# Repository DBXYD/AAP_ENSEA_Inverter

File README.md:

# ENSEA - Projet Onduleur Triphasé didactique, 60V, 10A
- Rédaction : Nicolas Papazoglou, Alexis Martin,
- Desgin et Réalisation : Nicolas Papazoglou, Alexis Martin, Patricia Kittel,
- Conseils : Pierre Toussaint.

# Présentation du projet

## Motivations
Dans le cadre de la formation des étudiants de l'ENSEA, les professeurs ont ressenti le besoin de créer une maquette pédagogique pour plusieurs raisons : 
* De nombreuses pannes récurentes sur les maquettes existantes,
* Réparations chronophages voir impossibles,
* L'ensemble du matériel est caché des étudiants, ils ne peuvent pas voir l'intérieur, le routage de la carte et les composants,
* Le coût de l'ensemble du matériel acheté est important.

## Objectifs
* Réalisation d'une maquette fiable pour les TPs d’électrotechnique et automatique : Gain en temps et en autonomie pour les étudiants,
* Feedback automatique en fonction des erreurs détectées : Gain en autonomie pour les étudiants, possibilité de travail hors séance sans
supervision d’un professeur,
* Projet open-source (disponible sur github),
* Compréhension globale possible par les étudiants, application de l’ensemble de leurs cours dans une maquette,
* Création modulaire, réutilisable dans d’autres cours/projets,
* Evolution possible à d’autres enseignements (buck/boost, 4Q, brushless, moteurs synchrones, asservissement, etc...),
* Maintenance facile et rapide

## Cahier des charges
* Onduleur triphasé 60V / 15A,
* Protections surtensions et surintensités,
* Commande de mise sous tension,
* Pilotage par liaison UART over USB,
* Utilisable en commande “brushless” : entrées position “hall” ,
* Utilisable en commande vectorielle ou MCC : entrée position “encoder”,
* Protection alimentation non réversible : module “freinage”,
* Vérification automatique des temps morts,
* Mesure de courants (hall) dans les 3 phases + entrée,
* Mesure de tension dans les 3 phases + entrée,
* Alimentation externe secteur,
* Affichage erreurs, intensité PWM (affiche externe),
* Sorties mesures de courants et PWMs,
* Boitier,
* Tenue thermique,
* Isolation galvanique.

# Guide d'utilisation

# Guide du développeur
La majorité des signaux sont disponibles sur les connecteurs morpho au format des cartes Nucleo-64.
Sur la base des cartes Nucleo, les connecteurs répérés CN7 et CN10 sont disponibles pour intégrer une carte custom.

## Connecteurs
### Connecteur CN7
| Type           | Label         | Pin number | Pin number | Label         | Type           |
|----------------|---------------|------------|------------|---------------|----------------|
| Digital Output | UART_TX_STM32 | 1          | 2          | UART_RX_STM32 | Digital Input  |
|                | N.C.          | 3          | 4          | NRST_STM32    | Digital Output |
|                | N.C.          | 5          | 6          | 5V            | Power Input    |
|                | N.C.          | 7          | 8          | GND           | Power Input    |
|                | N.C.          | 9          | 10         | N.C           |                |
|                | N.C.          | 11         | 12         | N.C           |                |
|                | N.C.          | 13         | 14         | N.C.          |                |
|                | N.C.          | 15         | 16         | N.C.          |                |
|                | N.C.          | 17         | 18         | N.C.          |                |
| Power Input    | GND           | 19         | 20         | GND           | Power Input    |
|                | N.C.          | 21         | 22         | GND           | Power Input    |
|                | N.C.          | 23         | 24         | N.C.          |                |
|                | N.C.          | 25         | 26         | N.C.          |                |
|                | N.C.          | 27         | 28         | Bus_V         | Analog Input   |
|                | N.C.          | 29         | 30         | U_Imes        | Analog Input   |
|                | N.C.          | 31         | 32         | Enc_B         | Digital Input  |
|                | N.C.          | 33         | 34         | W_Imes        | Analog Input   |
| Analog Input   | Bus_Imes      | 35         | 36         | W_Vph         | Analog Input   |
| Analog Input   | V_Vph         | 37         | 38         | U_Vph         | Analog Input   |

### Connecteur CN10
| Type           | Label         | Pin number |            | Label         | Type           |
|----------------|---------------|------------|------------|---------------|----------------|
|                | N.C.          | 1          | 2          | Enc_Z         | Digital Input  |
|                | N.C.          | 3          | 4          | N.C.          |                |
|                | N.C.          | 5          | 6          | N.C.          |                |
|                | N.C.          | 7          | 8          | N.C.          |                |
| Power Input    | GND           | 9          | 10         | N.C.          |                |
|                | N.C.          | 11         | 12         | N.C.          |                |
| Digital Input  | Enc_A         | 13         | 14         | N.C.          |                |
|                | N.C.          | 15         | 16         | N.C.          |                |
|                | N.C.          | 17         | 18         | N.C.          |                |
|                | N.C.          | 19         | 20         | GND           | Power Input    |
| Output         | V_PWM_H       | 21         | 22         | N.C.          |                |
| Output         | U_PWM_H       | 23         | 24         | V_Imes        | Analog Input   |
|                | N.C.          | 25         | 26         | W_PWM_L       | Output         |
|                | N.C.          | 27         | 28         | V_PWM_L       | Output         |
|                | N.C.          | 29         | 30         | U_PWM_L       | Output         |
|                | N.C.          | 31         | 32         | GND           | Power Input    |
| Output         | W_PWM_H       | 33         | 34         | N.C.          |                |
|                | N.C.          | 35         | 36         | N.C.          |                |
|                | N.C.          | 37         | 38         | N.C.          |                |

## Input / Output labels

### Communication avec le micro-controleur présent sur la carte-mère
* UART_TX_STM32 : UART vers le micro-controleur
* UART_RX_STM32 : UART depuis le micro-controleur
* NRST_STM32 : signal pour faire un reset du micro-controleur de la carte

### Communication avec le module encodeur
* Enc_A : entrée du signal A de l'encodeur
* Enc_B : entrée du signal B de l'encodeur
* Enc_Z : entrée du signal Z de l'encodeur

### Mesure de tension
* Bus_V : mesure de la tension du bus d'alimentation
* U_Vph : mesure de la tension de la sortie U (entre les 2 transistors)
* V_Vph : mesure de la tension de la sortie V (entre les 2 transistors)
* W_Vph : mesure de la tension de la sortie W (entre les 2 transistors)

### Mesure de courant
* Bus_Imes : mesure de courant du bus d'alimentation
* U_Imes
* V_Imes
* W_Imes

### Génération de PWM
* U_PWM_H
* U_PWM_L
* V_PWM_H
* V_PWM_L
* W_PWM_H
* W_PWM_L

# FAQ

# Pannes courantes 
## Dysfonctionnement des Mosfet
Plusieurs causes peuvent causer la destruction des transistors : 
* Non respect des temps mort,
* Commande provocant une freinage trop important : retour du courant chargeant les condensateurs sur le bus d'alimentation. Ceci provoque la montée en tension du bus au-delà des spécifications des transistor de puissance

Détection de la panne : 
* Débrancher l'ensemble des câbles de la maquette, et le cas échéant, attendre que les condensateurs du bus d'alimentation soient totalement vides.
* A l'aide d'un multimètre, en mode diode, tester la continuité entre :
  - Entre la sortie U et le bus d'alimentation (Q202)
  - Entre la sortie U et la masse (Q203)
  - Entre la sortie V et le bus d'alimentation (Q302)
  - Entre la sortie V et la masse (Q303)
  - Entre la sortie W et le bus d'alimentation (Q402)
  - Entre la sortie W et la masse (Q403)
* Le fonctionnement normal est l'absence de continuité électrique. Dans le cas d'une continuité, le transistor en question est HS, il doit donc être changé.

# Composants
* Drivers de Mosfet/optocoupleur : HCPL-315J, Optocoupleurs sortie logique 0.5A IGBT Gate Drive [link](https://www.mouser.fr/ProductDetail/Broadcom-Avago/HCPL-315J?qs=s%252BgfxR24RQ4lntGToXJAvA%3D%3D)
* Transistor MOSFET : IRF540NPBF, MOSFET de puissance, Canal N, 100 V, 33 A, 0.044 ohm, TO-220AB, Traversant [Link](https://fr.farnell.com/infineon/irf540npbf/transistor-mosfet-canal-n-to220/dp/8648298?st=irf540n)
* Capteur de Courant : GO 10-SME/SP3, Capteur de courant, 300 kHz, SOIC, 8 Broche(s), 3.135 V, 3.465 V [Link](https://fr.farnell.com/lem/go-10-sme-sp3/capteur-courant-300khz-soic-8/dp/3796461?st=GO%2010-SME/SP3)
* Power supply : MP-LD30-23B15R2 - Alimentation montage PCB AC/DC (PSU), ITE, Équipements Ménagers et Transformateurs, 1 sortie [link](https://fr.farnell.com/multicomp-pro/mp-ld30-23b15r2/power-supply-ac-dc-15v-2a/dp/3780527)
* Power regulator : Input : 5V DC, Output : 3.3V DC, AZ1117CH-3.3TRG1 - LDO, FIXE, 3,3V, 0.8A, -20 A 125°C [link](https://fr.farnell.com/diodes-inc/az1117ch-3-3trg1/ldo-fixe-3-3v-0-8a-20-a-125-c/dp/3483073RL)
* Alimentation 15V/400mA isolé : MPRB2415S-6W - Conv. DC/DC, montage traversant isolé, ITE, 4:1, 6 W, 1 sortie, 15 V, 400 mA [link](https://fr.farnell.com/multicomp-pro/mprb2415s-6w/convertisseur-dc-dc-15v-0-4a/dp/3652723)
* Alimentation 5V/200mA isolé : 17791063215 - MagI³C-VISM Variable Isolated SIP Module, [Link](https://www.we-online.com/components/products/datasheet/17791063215.pdf)
* Connector : PX0580/PC Connecteur de puissance IEC, Entrée IEC C14, 10 A, 250 VAC, Traversant [link](https://fr.farnell.com/bulgin/px0580-pc/embase-iec-c14-carte-proto-10a/dp/313853)
* Screen : MDOB128064XV-YI - OLED graphique, 128 x 64 pixels, Jaune sur noir, 3.3V, I2C, 35.5mm x 32mm, -40 °C [Link](https://fr.farnell.com/midas/mdob128064xv-yi/afficheur-oled-cob-128-x-64-pix/dp/3407293)
* Break resistor : 162-3488 - Résistance à montage sur châssis Aluminium, 5Ω 100W ±1% [Link](https://fr.rs-online.com/web/p/resistances-a-montage-sur-chassis/1623488)
* Break schottky : VS-15TQ060S-M3 - Redresseur Schottky, 60 V, 15 A, Une, TO-263AB, 3 Broche(s), 620 mV [Link](https://fr.farnell.com/vishay/vs-15tq060s-m3/diode-schottky-simple-60v-to263ab/dp/2909608?ost=2909608)

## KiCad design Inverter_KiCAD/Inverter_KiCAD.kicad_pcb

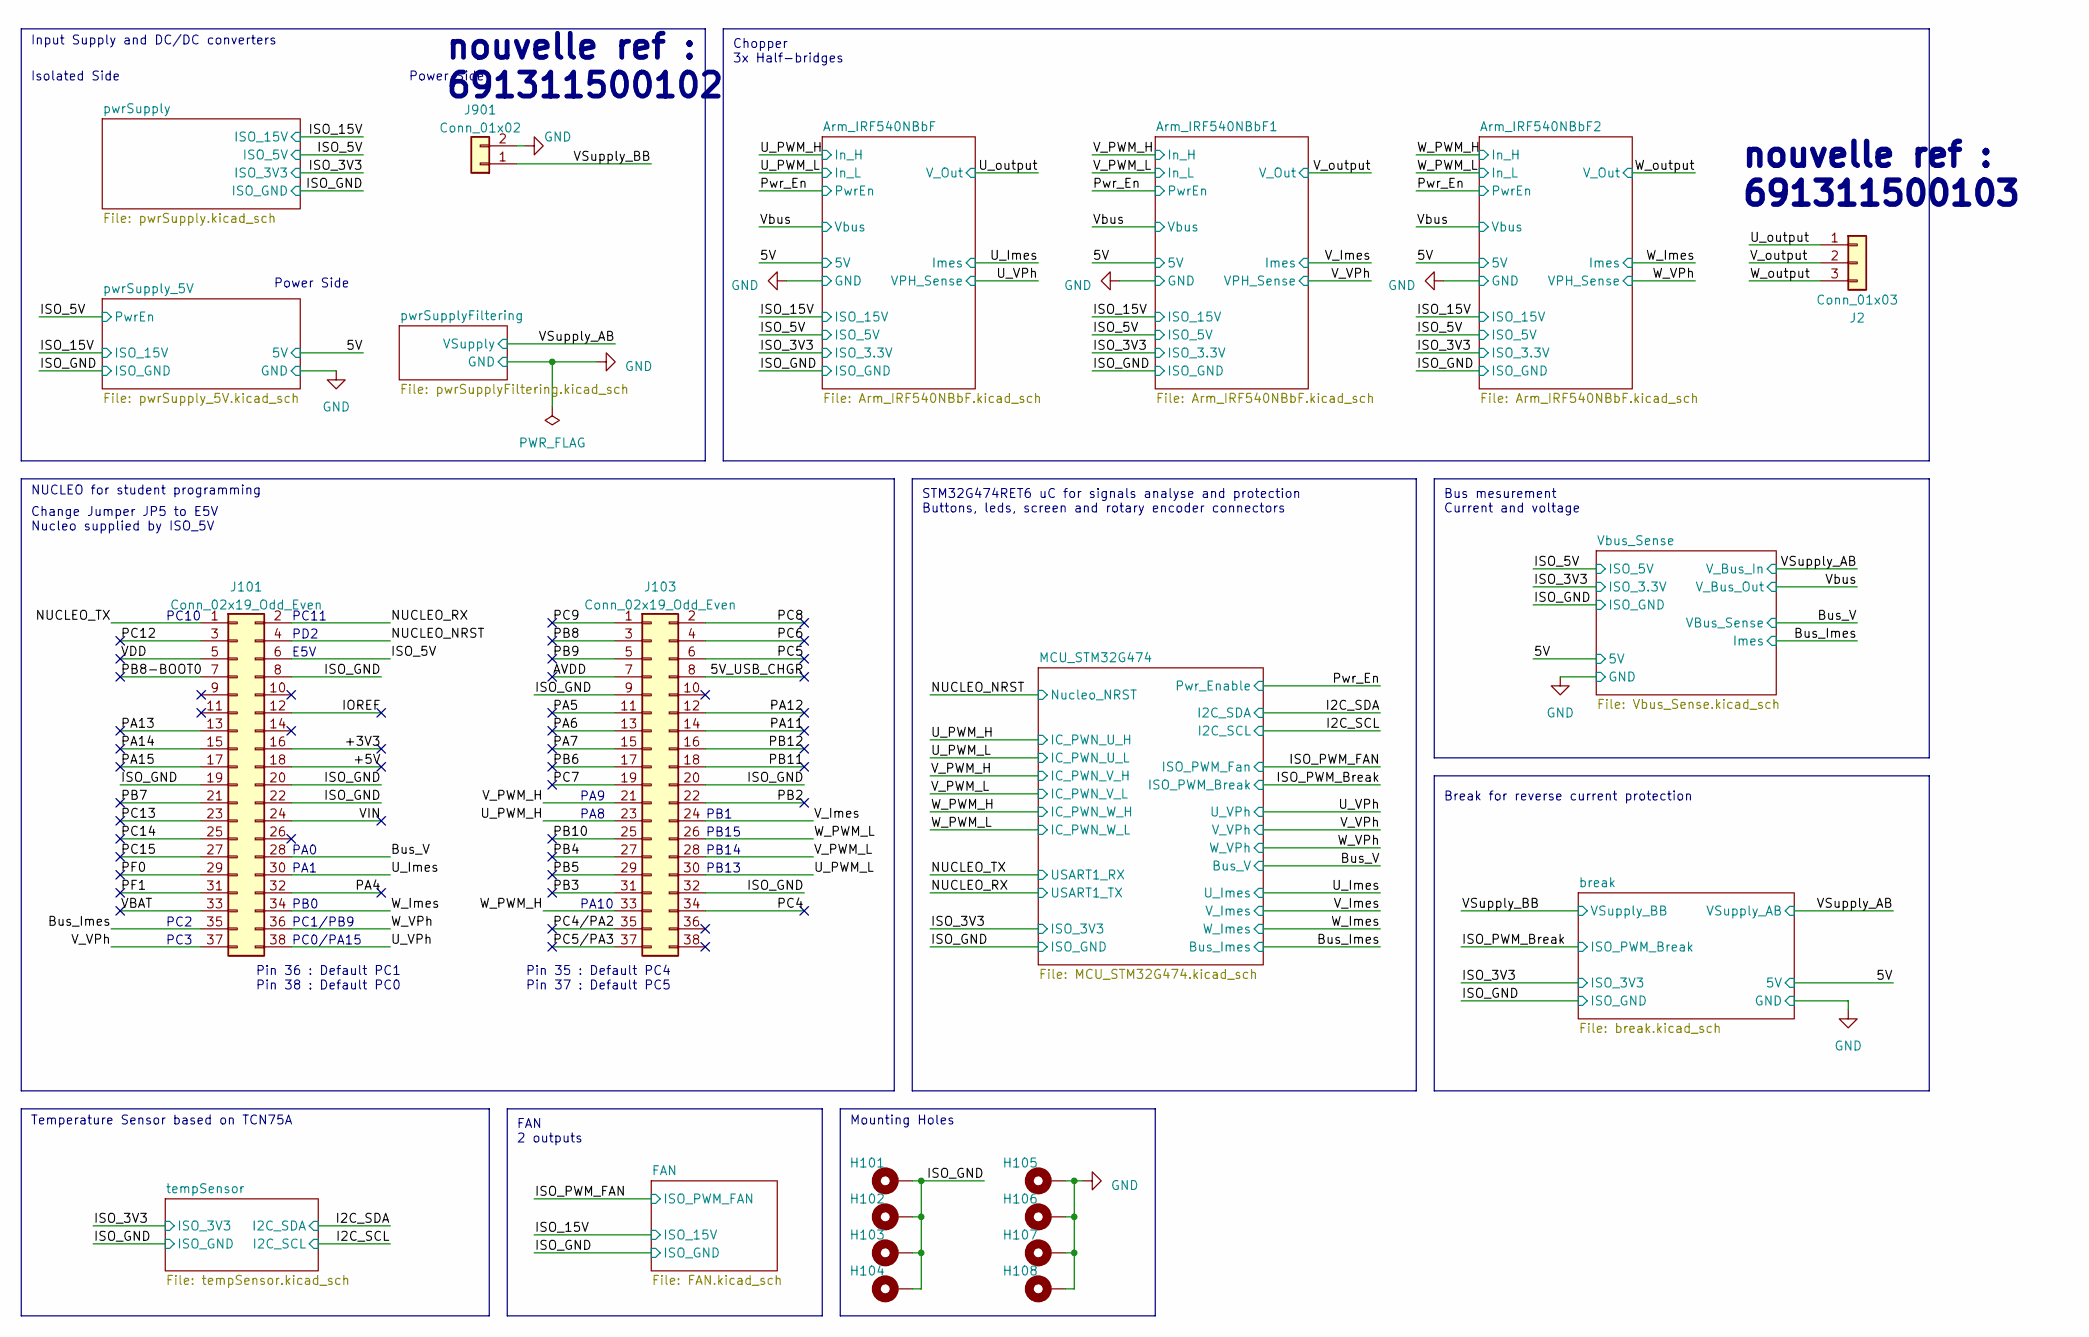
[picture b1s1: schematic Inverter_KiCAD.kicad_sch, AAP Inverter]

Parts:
H101, H102, H103, H104, H105, H106, H107, H108: MountingHole_Pad; MountingHole_3.2mm_M3_Pad_Via
J2: Conn_01x03; 691311700003
J101, J103: Conn_02x19_Odd_Even; PinHeader_2x19_P2.54mm_Vertical
J901: Conn_01x02; 691311700002

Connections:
/5V_USB_CHGR: J103.8
/+3V3: J101.16
/+5V: J101.18
/AVDD: J103.7
/Bus_Imes: J101.35; also elsewhere on the board
/Bus_V: J101.28; also elsewhere on the board
/IOREF: J101.12
/ISO_5V: J101.6; also elsewhere on the board
/ISO_GND: H101.1, H102.1, H103.1, H104.1, J101.8, J101.19, J101.20, J101.22, J103.9, J103.20, J103.32; also elsewhere on the board
/NUCLEO_NRST: J101.4; also elsewhere on the board
/NUCLEO_RX: J101.2; also elsewhere on the board
/NUCLEO_TX: J101.1; also elsewhere on the board
/PA4: J101.32
/PA5: J103.11
/PA6: J103.13
/PA7: J103.15
/PA11: J103.14
/PA12: J103.12
/PA13: J101.13
/PA14: J101.15
/PA15: J101.17
/PB2: J103.22
/PB3: J103.31
/PB4: J103.27
/PB5: J103.29
/PB6: J103.17
/PB7: J101.21
/PB8: J103.3
/PB8-BOOT0: J101.7
/PB9: J103.5
/PB10: J103.25
/PB11: J103.18
/PB12: J103.16
/PC4: J103.34
/PC4/PA2: J103.35
/PC5: J103.6
/PC5/PA3: J103.37
/PC6: J103.4
/PC7: J103.19
/PC8: J103.2
/PC9: J103.1
/PC12: J101.3
/PC13: J101.23
/PC14: J101.25
/PC15: J101.27
/PF0: J101.29
/PF1: J101.31
/U_Imes: J101.30; also elsewhere on the board
/U_PWM_H: J103.23; also elsewhere on the board
/U_PWM_L: J103.30; also elsewhere on the board
/U_VPh: J101.38; also elsewhere on the board
/U_output: J2.1; also elsewhere on the board
/VBAT: J101.33
/VDD: J101.5
/VIN: J101.24
/V_Imes: J103.24; also elsewhere on the board
/V_PWM_H: J103.21; also elsewhere on the board
/V_PWM_L: J103.28; also elsewhere on the board
/V_VPh: J101.37; also elsewhere on the board
/V_output: J2.2; also elsewhere on the board
/W_Imes: J101.34; also elsewhere on the board
/W_PWM_H: J103.33; also elsewhere on the board
/W_PWM_L: J103.26; also elsewhere on the board
/W_VPh: J101.36; also elsewhere on the board
/W_output: J2.3; also elsewhere on the board
/break/Break_Drain_Mosfet: J901.1; also elsewhere on the board

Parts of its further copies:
J1: Conn_01x02; 691311700002

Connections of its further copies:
/VSupply_BB: J1.1; also elsewhere on the board

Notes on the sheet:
PB14
PC10
Input Supply and DC/DC converters
Temperature Sensor based on TCN75A
PC3
nouvelle ref : 691311500103
PA8
Mounting Holes
NUCLEO for student programming
Pin 35 : Default PC4 Pin 37 : Default PC5
PA10
STM32G474RET6 uC for signals analyse and protection Buttons, leds, screen and rotary encoder connectors
Break for reverse current protection
PB13
Chopper 3x Half-bridges
PA0
PC0/PA15
PD2
nouvelle ref : 691311500102
E5V
PB0
PA9
Power Side
Isolated Side
PC11
FAN 2 outputs
PA1
Pin 36 : Default PC1 Pin 38 : Default PC0
PC1/PB9
PB1
PC2
Bus mesurement Current and voltage
PB15
Change Jumper JP5 to E5V Nucleo supplied by ISO_5V

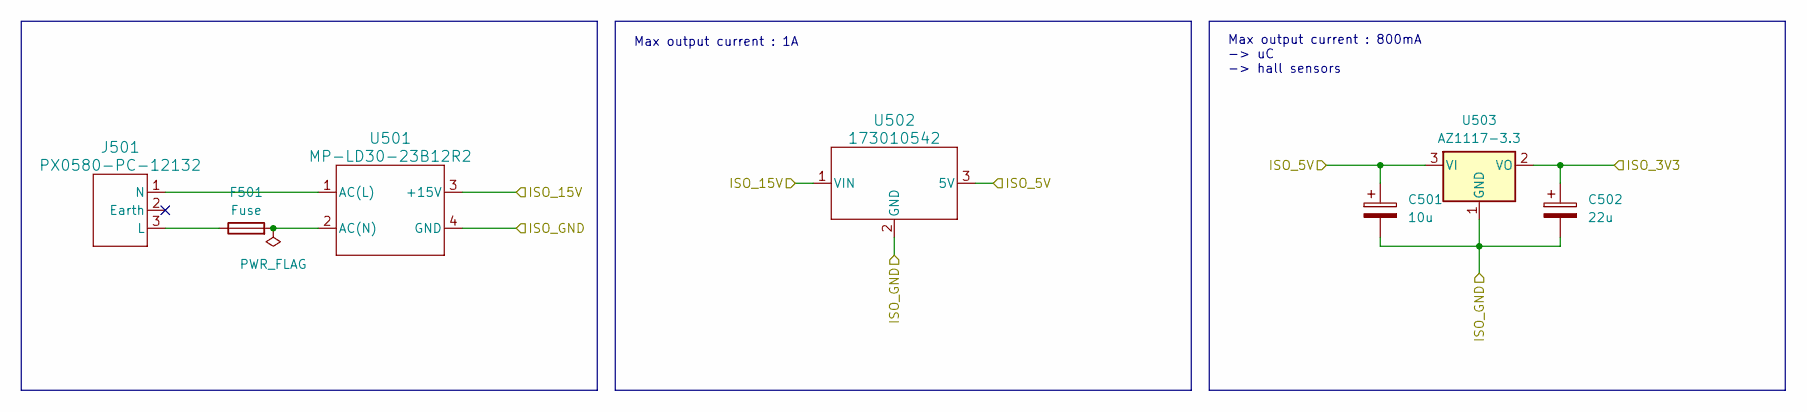
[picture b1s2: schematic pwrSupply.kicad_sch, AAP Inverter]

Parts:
C501: 10u; CP_Elec_4x5.4
C502: 22u; CP_Elec_5x5.4
F501: Fuse; 0031.8201
J501: PX0580-PC-12132
U501: MP-LD30-23B12R2; MP-LD30-23B15R2
U502: 173010542; 173010578
U503: AZ1117-3.3; SOT-223-3_TabPin2

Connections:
/ISO_3V3: C502.1, U503.2 (VO); also elsewhere on the board
/ISO_5V: C501.1, U502.3 (5V), U503.3 (VI); also elsewhere on the board
/ISO_15V: U501.3 (+15V), U502.1 (VIN); also elsewhere on the board
/ISO_GND: C501.2, C502.2, U501.4 (GND), U502.2 (GND), U503.1 (GND); also elsewhere on the board
unnamed: F501.1, J501.3 (L)
unnamed: J501.1 (N), U501.1 (AC(L))
unnamed: F501.2, U501.2 (AC(N))

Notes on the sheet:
Max output current : 800mA -> uC -> hall sensors
Max output current : 1A

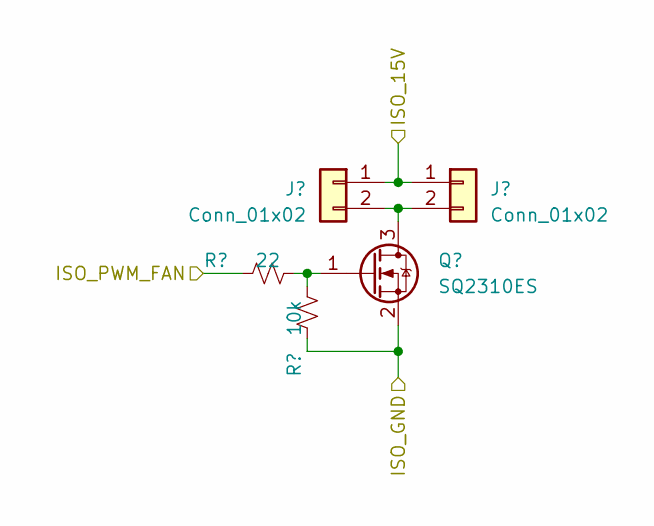
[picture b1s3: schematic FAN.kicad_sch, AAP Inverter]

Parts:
J1101, J1102: Conn_01x02; JST_XH_B2B-XH-A_1x02_P2.50mm_Vertical
Q1101: SQ2310ES; SOT-23
R1101: 22; R_0402_1005Metric_Pad0.72x0.64mm_HandSolder
R1102: 10k; R_0402_1005Metric_Pad0.72x0.64mm_HandSolder

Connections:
/ISO_15V: J1101.1, J1102.1; also elsewhere on the board
/ISO_GND: Q1101.2 (S), R1102.2; also elsewhere on the board
/ISO_PWM_FAN: R1101.2; also elsewhere on the board
unnamed: J1101.2, J1102.2, Q1101.3 (D)
unnamed: Q1101.1 (G), R1101.1, R1102.1

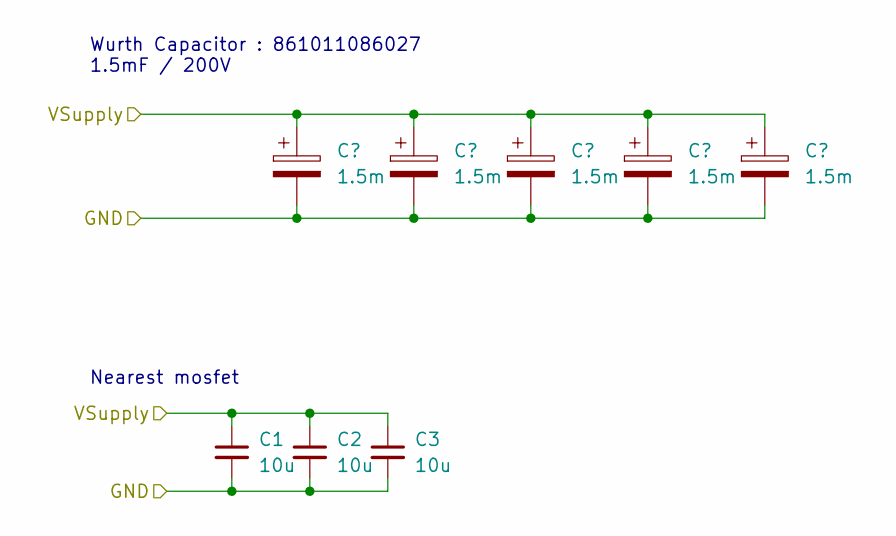
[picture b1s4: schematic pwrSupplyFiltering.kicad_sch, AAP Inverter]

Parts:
C1, C2, C3: 10u; C_0805_2012Metric
C1005, C1006, C1007, C1008, C1009: 1.5m; CP_Radial_D35.0mm_P10.00mm_SnapIn

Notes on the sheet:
Wurth Capacitor : 861011086027 1.5mF / 200V
Nearest mosfet

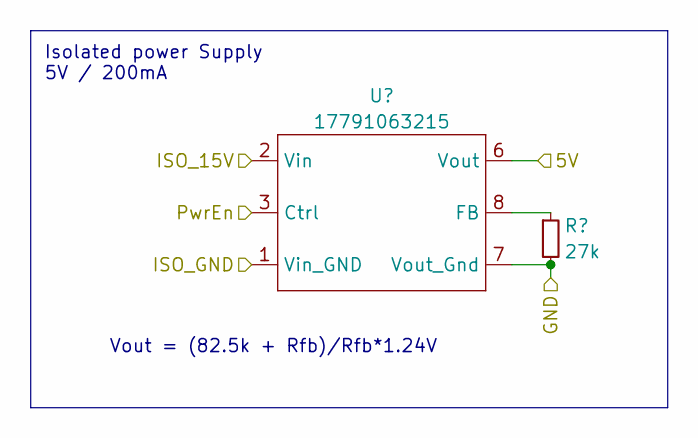
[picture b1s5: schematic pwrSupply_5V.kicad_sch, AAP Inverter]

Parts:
R701: 27k; R_0402_1005Metric_Pad0.72x0.64mm_HandSolder
U701: 17791063215

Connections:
/5V: U701.6 (Vout); also elsewhere on the board
/ISO_5V: U701.3 (Ctrl); also elsewhere on the board
/ISO_15V: U701.2 (Vin); also elsewhere on the board
/ISO_GND: U701.1 (Vin_GND); also elsewhere on the board
unnamed: R701.1, U701.8 (FB)

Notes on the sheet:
Vout = (82.5k + Rfb)/Rfb*1.24V
Isolated power Supply 5V / 200mA

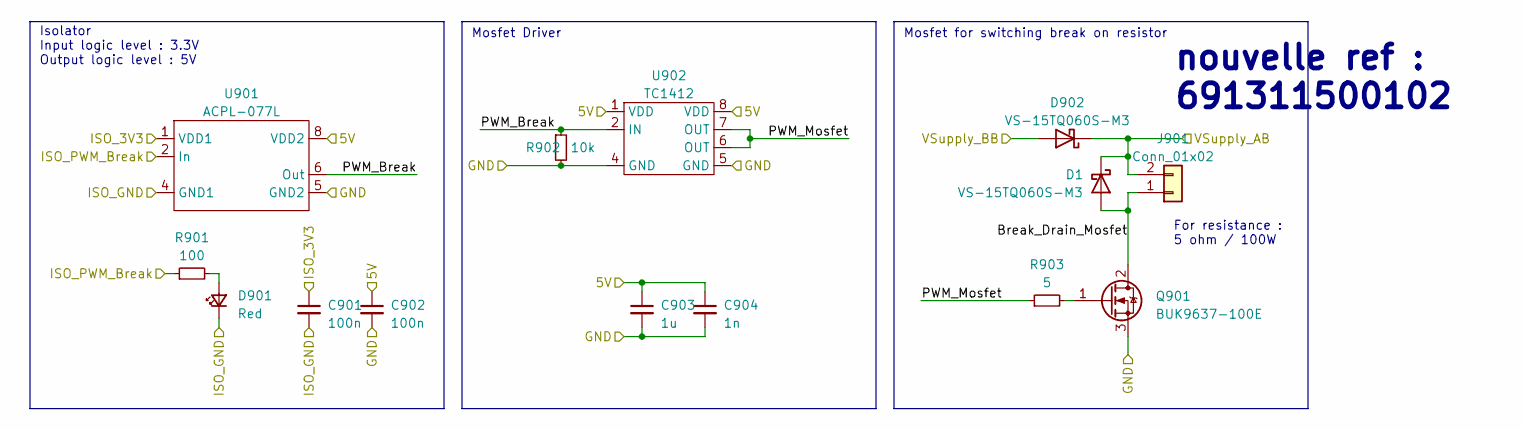
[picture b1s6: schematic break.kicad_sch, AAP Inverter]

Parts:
C901, C902: 100n; C_0402_1005Metric_Pad0.74x0.62mm_HandSolder
C903: 1u; C_0402_1005Metric_Pad0.74x0.62mm_HandSolder
C904: 1n; C_0402_1005Metric_Pad0.74x0.62mm_HandSolder
D1, D902: VS-15TQ060S-M3; TO-263-2
D901: Red; LED_0603_1608Metric_Pad1.05x0.95mm_HandSolder
J901: Conn_01x02; 691311700002
Q901: BUK9637-100E; TO-263-2
R901: 100; R_0402_1005Metric_Pad0.72x0.64mm_HandSolder
R902: 10k; R_0402_1005Metric_Pad0.72x0.64mm_HandSolder
R903: 5; R_1206_3216Metric_Pad1.30x1.75mm_HandSolder
U901: ACPL-077L; SO-8_3.9x4.9mm_P1.27mm
U902: TC1412; SOIC-8_3.9x4.9mm_P1.27mm

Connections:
/5V: C902.1, C903.1, C904.1, U901.8 (VDD2), U902.1 (VDD), U902.8 (VDD); also elsewhere on the board
/ISO_3V3: C901.1, U901.1 (VDD1); also elsewhere on the board
/ISO_GND: C901.2, D901.1 (K), U901.4 (GND1); also elsewhere on the board
/ISO_PWM_Break: R901.1, U901.2 (In); also elsewhere on the board
/VSupply_BB: D902.3 (A); also elsewhere on the board
/break/Break_Drain_Mosfet: D1.3 (A), J901.1, Q901.2 (D)
/break/PWM_Break: R902.1, U901.6 (Out), U902.2 (IN)
/break/PWM_Mosfet: R903.1, U902.6 (OUT), U902.7 (OUT)
unnamed: D901.2 (A), R901.2
unnamed: Q901.1 (G), R903.2

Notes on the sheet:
Isolator Input logic level : 3.3V Output logic level : 5V
nouvelle ref : 691311500102
For resistance : 5 ohm / 100W
Mosfet for switching break on resistor
Mosfet Driver

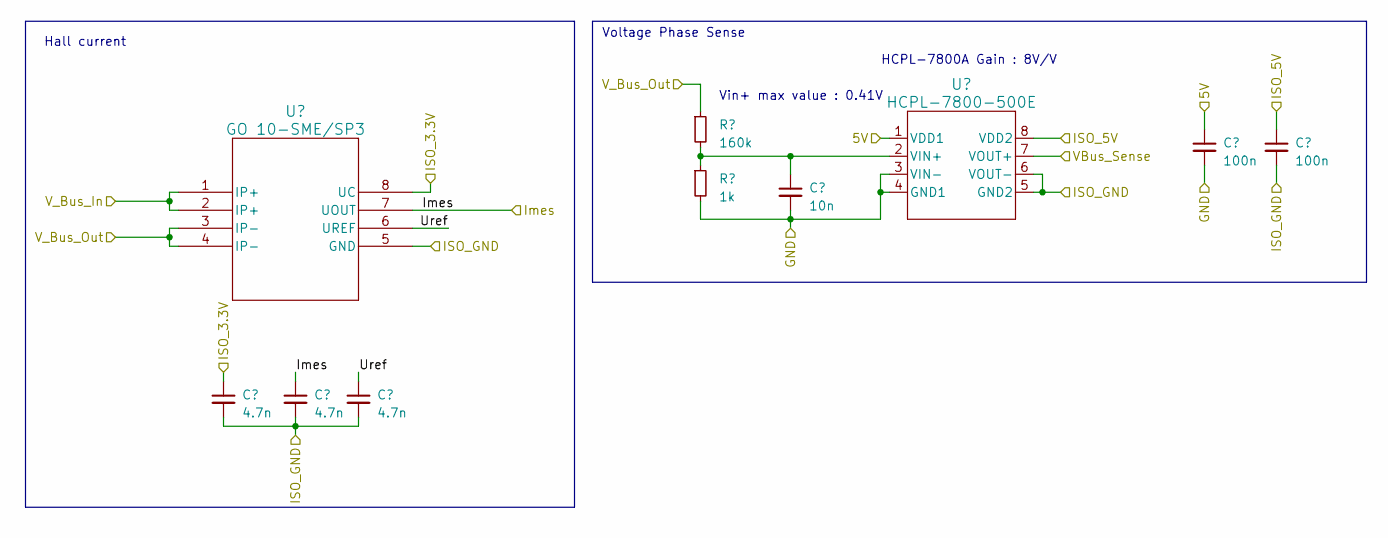
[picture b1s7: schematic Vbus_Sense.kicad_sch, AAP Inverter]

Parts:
C601, C602, C603: 4.7n; C_0402_1005Metric_Pad0.74x0.62mm_HandSolder
C604: 10n; C_0402_1005Metric_Pad0.74x0.62mm_HandSolder
C605, C606: 100n; C_0402_1005Metric_Pad0.74x0.62mm_HandSolder
R601: 160k; R_0402_1005Metric_Pad0.72x0.64mm_HandSolder
R602: 1k; R_0402_1005Metric_Pad0.72x0.64mm_HandSolder
U601: GO 10-SME/SP3; SOIC8-GO-SME&slash_SP3_LEM
U602: HCPL-7800-500E; DIP-8 Gull Wing

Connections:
/5V: C605.1, U602.1 (VDD1); also elsewhere on the board
/Bus_Imes: C602.1, U601.7 (UOUT); also elsewhere on the board
/Bus_V: U602.7 (VOUT+); also elsewhere on the board
/ISO_3V3: C601.1, U601.8 (UC); also elsewhere on the board
/ISO_5V: C606.1, U602.8 (VDD2); also elsewhere on the board
/ISO_GND: C601.2, C602.2, C603.2, C606.2, U601.5 (GND), U602.5 (GND2), U602.6 (VOUT-); also elsewhere on the board
/Vbus: R601.1, U601.3 (IP-), U601.4 (IP-); also elsewhere on the board
/Vbus_Sense/Uref: C603.1, U601.6 (UREF)
unnamed: C604.1, R601.2, R602.1, U602.2 (VIN+)

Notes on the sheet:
Hall current
Vin+ max value : 0.41V
HCPL-7800A Gain : 8V/V
Voltage Phase Sense

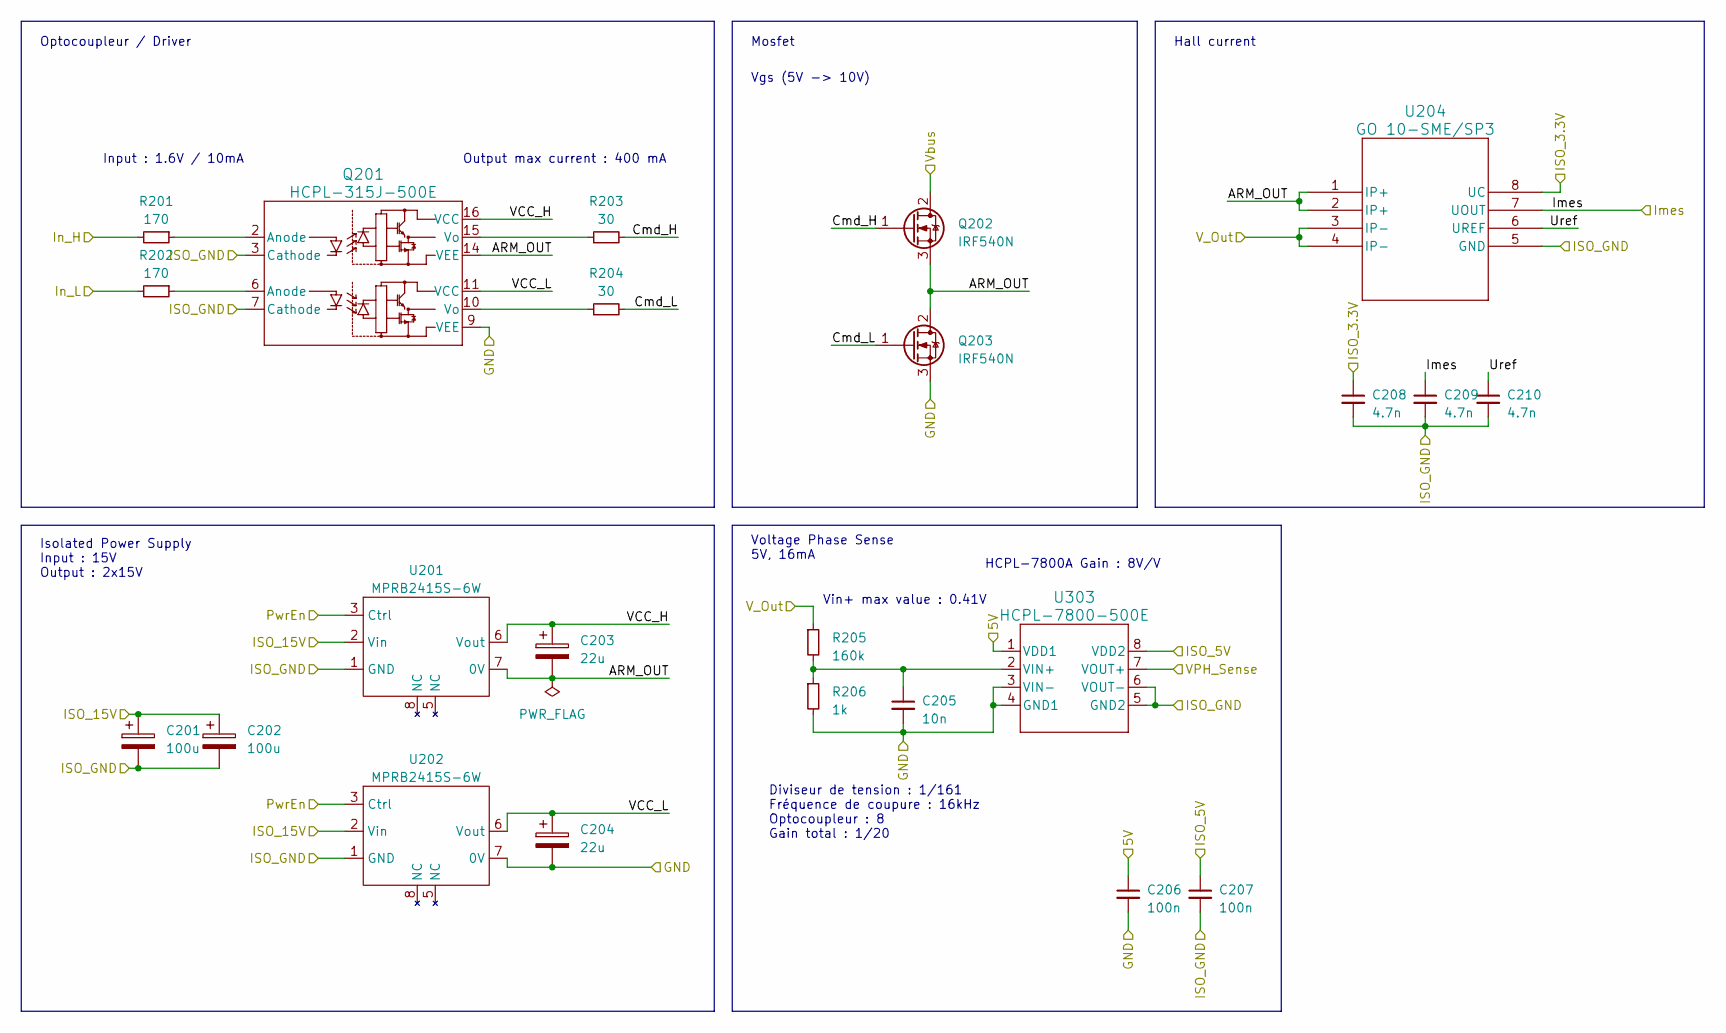
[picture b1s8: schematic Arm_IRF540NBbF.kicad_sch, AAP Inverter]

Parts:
C201, C202: 100u; CP_Elec_6.3x7.7
C203, C204: 22u; CP_Elec_5x5.4
C205: 10n; C_0402_1005Metric_Pad0.74x0.62mm_HandSolder
C206, C207: 100n; C_0402_1005Metric_Pad0.74x0.62mm_HandSolder
C208, C209, C210: 4.7n; C_0402_1005Metric_Pad0.74x0.62mm_HandSolder
Q201: HCPL-315J-500E; SO-16_HCPL-315J_BRA
Q202, Q203: IRF540N; TO-220-3_Vertical
R201, R202: 170; R_0402_1005Metric_Pad0.72x0.64mm_HandSolder
R203, R204: 30; R_1206_3216Metric_Pad1.30x1.75mm_HandSolder
R205: 160k; R_0402_1005Metric_Pad0.72x0.64mm_HandSolder
R206: 1k; R_0402_1005Metric_Pad0.72x0.64mm_HandSolder
U201, U202: MPRB2415S-6W; MPRB2415S
U204: GO 10-SME/SP3; SOIC8-GO-SME&slash_SP3_LEM
U303: HCPL-7800-500E; DIP-8 Gull Wing

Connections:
/5V: C206.1, U303.1 (VDD1); also elsewhere on the board
/Arm_IRF540NBbF/ARM_OUT: C203.2, Q201.14 (VEE), Q202.3 (S), Q203.2 (D), U201.7 (0V), U204.1 (IP+), U204.2 (IP+)
/Arm_IRF540NBbF/Cmd_H: Q202.1 (G), R203.2
/Arm_IRF540NBbF/Cmd_L: Q203.1 (G), R204.2
/Arm_IRF540NBbF/Uref: C210.1, U204.6 (UREF)
/Arm_IRF540NBbF/VCC_H: C203.1, Q201.16 (VCC), U201.6 (Vout)
/Arm_IRF540NBbF/VCC_L: C204.1, Q201.11 (VCC), U202.6 (Vout)
/ISO_3V3: C208.1, U204.8 (UC); also elsewhere on the board
/ISO_5V: C207.1, U303.8 (VDD2); also elsewhere on the board
/ISO_15V: C201.1, C202.1, U201.2 (Vin), U202.2 (Vin); also elsewhere on the board
/ISO_GND: C201.2, C202.2, C207.2, C208.2, C209.2, C210.2, Q201.3 (Cathode), Q201.7 (Cathode), U201.1 (GND), U202.1 (GND), U204.5 (GND), U303.5 (GND2), U303.6 (VOUT-); also elsewhere on the board
/Pwr_En: U201.3 (Ctrl), U202.3 (Ctrl); also elsewhere on the board
/U_Imes: C209.1, U204.7 (UOUT); also elsewhere on the board
/U_PWM_H: R201.2; also elsewhere on the board
/U_PWM_L: R202.2; also elsewhere on the board
/U_output: R205.1, U204.3 (IP-), U204.4 (IP-); also elsewhere on the board
/V_VPh: U303.7 (VOUT+); also elsewhere on the board
/Vbus: Q202.2 (D); also elsewhere on the board
unnamed: Q201.2 (Anode), R201.1
unnamed: Q201.6 (Anode), R202.1
unnamed: Q201.10 (Vo), R204.1
unnamed: Q201.15 (Vo), R203.1

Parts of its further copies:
C301, C302, C401, C402: 100u; CP_Elec_6.3x7.7
C303, C304, C403, C404: 22u; CP_Elec_5x5.4
C305, C405: 10n; C_0402_1005Metric_Pad0.74x0.62mm_HandSolder
C306, C307, C406, C407: 100n; C_0402_1005Metric_Pad0.74x0.62mm_HandSolder
C308, C309, C310, C408, C409, C410: 4.7n; C_0402_1005Metric_Pad0.74x0.62mm_HandSolder
Q301, Q401: HCPL-315J-500E; SO-16_HCPL-315J_BRA
Q302, Q303, Q402, Q403: IRF540N; TO-220-3_Vertical
R301, R302, R401, R402: 170; R_0402_1005Metric_Pad0.72x0.64mm_HandSolder
R303, R304, R403, R404: 30; R_1206_3216Metric_Pad1.30x1.75mm_HandSolder
R305, R405: 160k; R_0402_1005Metric_Pad0.72x0.64mm_HandSolder
R306, R406: 1k; R_0402_1005Metric_Pad0.72x0.64mm_HandSolder
U203, U403: HCPL-7800-500E; DIP-8 Gull Wing
U301, U302, U401, U402: MPRB2415S-6W; MPRB2415S
U304, U404: GO 10-SME/SP3; SOIC8-GO-SME&slash_SP3_LEM

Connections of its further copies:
/5V: C306.1, C406.1, U203.1 (VDD1), U403.1 (VDD1); also elsewhere on the board
/Arm_IRF540NBbF1/ARM_OUT: C303.2, Q301.14 (VEE), Q302.3 (S), Q303.2 (D), U301.7 (0V), U304.1 (IP+), U304.2 (IP+)
/Arm_IRF540NBbF1/Cmd_H: Q302.1 (G), R303.2
/Arm_IRF540NBbF1/Cmd_L: Q303.1 (G), R304.2
/Arm_IRF540NBbF1/Uref: C310.1, U304.6 (UREF)
/Arm_IRF540NBbF1/VCC_H: C303.1, Q301.16 (VCC), U301.6 (Vout)
/Arm_IRF540NBbF1/VCC_L: C304.1, Q301.11 (VCC), U302.6 (Vout)
/Arm_IRF540NBbF2/ARM_OUT: C403.2, Q401.14 (VEE), Q402.3 (S), Q403.2 (D), U401.7 (0V), U404.1 (IP+), U404.2 (IP+)
/Arm_IRF540NBbF2/Cmd_H: Q402.1 (G), R403.2
/Arm_IRF540NBbF2/Cmd_L: Q403.1 (G), R404.2
/Arm_IRF540NBbF2/Uref: C410.1, U404.6 (UREF)
/Arm_IRF540NBbF2/VCC_H: C403.1, Q401.16 (VCC), U401.6 (Vout)
/Arm_IRF540NBbF2/VCC_L: C404.1, Q401.11 (VCC), U402.6 (Vout)
/ISO_3V3: C308.1, C408.1, U304.8 (UC), U404.8 (UC); also elsewhere on the board
/ISO_5V: C307.1, C407.1, U203.8 (VDD2), U403.8 (VDD2); also elsewhere on the board
/ISO_15V: C301.1, C302.1, C401.1, C402.1, U301.2 (Vin), U302.2 (Vin), U401.2 (Vin), U402.2 (Vin); also elsewhere on the board
/ISO_GND: C301.2, C302.2, C307.2, C308.2, C309.2, C310.2, C401.2, C402.2, C407.2, C408.2, C409.2, C410.2, Q301.3 (Cathode), Q301.7 (Cathode), Q401.3 (Cathode), Q401.7 (Cathode), U203.5 (GND2), U203.6 (VOUT-), U301.1 (GND), U302.1 (GND), U304.5 (GND), U401.1 (GND), U402.1 (GND), U403.5 (GND2), U403.6 (VOUT-), U404.5 (GND); also elsewhere on the board
/Pwr_En: U301.3 (Ctrl), U302.3 (Ctrl), U401.3 (Ctrl), U402.3 (Ctrl); also elsewhere on the board
/U_VPh: U203.7 (VOUT+); also elsewhere on the board
/V_Imes: C309.1, U304.7 (UOUT); also elsewhere on the board
/V_PWM_H: R301.2; also elsewhere on the board
/V_PWM_L: R302.2; also elsewhere on the board
/V_output: R305.1, U304.3 (IP-), U304.4 (IP-); also elsewhere on the board
/Vbus: Q302.2 (D), Q402.2 (D); also elsewhere on the board
/W_Imes: C409.1, U404.7 (UOUT); also elsewhere on the board
/W_PWM_H: R401.2; also elsewhere on the board
/W_PWM_L: R402.2; also elsewhere on the board
/W_VPh: U403.7 (VOUT+); also elsewhere on the board
/W_output: R405.1, U404.3 (IP-), U404.4 (IP-); also elsewhere on the board
unnamed: Q301.2 (Anode), R301.1
unnamed: Q301.6 (Anode), R302.1
unnamed: Q301.10 (Vo), R304.1
unnamed: Q301.15 (Vo), R303.1
unnamed: Q401.2 (Anode), R401.1
unnamed: Q401.6 (Anode), R402.1
unnamed: Q401.10 (Vo), R404.1
unnamed: Q401.15 (Vo), R403.1
unnamed: C405.1, R405.2, R406.1, U403.2 (VIN+)

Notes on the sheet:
Hall current
Isolated Power Supply Input : 15V Output : 2x15V
Output max current : 400 mA
Input : 1.6V / 10mA
Voltage Phase Sense 5V, 16mA
Vgs (5V -> 10V)
Vin+ max value : 0.41V
Mosfet
Optocoupleur / Driver
Diviseur de tension : 1/161 Fréquence de coupure : 16kHz Optocoupleur : 8 Gain total : 1/20
HCPL-7800A Gain : 8V/V

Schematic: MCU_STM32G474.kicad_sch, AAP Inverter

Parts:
C801, C802: 18p; C_0402_1005Metric_Pad0.74x0.62mm_HandSolder
C803, C806, C813: 10u; C_0603_1608Metric_Pad1.08x0.95mm_HandSolder
C804, C807, C808, C809, C810, C811, C812, C814, C815, C816, C817, C818: 100n; C_0402_1005Metric_Pad0.74x0.62mm_HandSolder
C805: 1u; C_0402_1005Metric_Pad0.74x0.62mm_HandSolder
D801, D802, D803, D804: LED; LED_0603_1608Metric_Pad1.05x0.95mm_HandSolder
J801: USB_C_Receptacle_USB2.0; USB_C_Receptacle_HRO_TYPE-C-31-M-12
J802: Conn_01x05; JST_XH_B5B-XH-A_1x05_P2.50mm_Vertical
J803: Conn_ST_STDC14; PinHeader_2x07_P1.27mm_Vertical_SMD
J804: Conn_01x04; JST_XH_B4B-XH-A_1x04_P2.50mm_Vertical
L801: 39n; L_0603_1608Metric_Pad1.05x0.95mm_HandSolder
R801: 10k; R_0402_1005Metric_Pad0.72x0.64mm_HandSolder
R802, R803: 5.1k; R_0402_1005Metric_Pad0.72x0.64mm_HandSolder
R804, R805, R806, R807: 340; R_0402_1005Metric_Pad0.72x0.64mm_HandSolder
SW801, SW802, SW803, SW804, SW805: SW_Push; 435451019820
U801: STM32G474RETx; LQFP-64_10x10mm_P0.5mm
U802: USBLC6-2SC6; SOT-23-6
Y801: 16M; ABLS-7.3728MHZ-CL-RESR-A-1-G-F

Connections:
/Bus_Imes: U801.36 (PB14); also elsewhere on the board
/Bus_V: U801.34 (PB12); also elsewhere on the board
/I2C_SCL: J804.3, U801.43 (PA9); also elsewhere on the board
/I2C_SDA: J804.4, U801.42 (PA8); also elsewhere on the board
/ISO_3V3: C803.1, C804.1, C806.2, C808.1, C809.1, C811.1, C812.1, C813.1, J802.1, J803.3 (VCC), J804.1, L801.1, U801.1 (VBAT), U801.16 (VDD), U801.32 (VDD), U801.48 (VDD), U801.64 (VDD); also elsewhere on the board
/ISO_GND: C801.1, C802.1, C803.2, C804.2, C805.2, C806.1, C807.2, C808.2, C809.2, C810.2, C811.2, C812.2, C813.2, C814.2, C815.2, C816.2, C817.2, C818.2, J801.A1 (GND), J801.A12 (GND), J801.B1 (GND), J801.B12 (GND), J801.S1 (SHIELD), J802.2, J803.5 (GND), J803.7 (GND), J803.11 (GNDDetect), J804.2, R801.2, R802.2, R803.2, R804.2, R805.2, R806.2, R807.2, SW801.2, SW802.2, SW803.2, SW804.2, SW805.2, U801.15 (VSS), U801.27 (VSSA), U801.31 (VSS), U801.47 (VSS), U801.63 (VSS), U802.2 (GND); also elsewhere on the board
/ISO_PWM_Break: U801.58 (PB5); also elsewhere on the board
/ISO_PWM_FAN: U801.57 (PB4); also elsewhere on the board
/MCU_STM32G474/D+: J801.A6 (D+), J801.B6 (D+), U802.6 (I/O1)
/MCU_STM32G474/D-: J801.A7 (D-), J801.B7 (D-), U802.4 (I/O2)
/MCU_STM32G474/ENC_A: J802.3, U801.20 (PA6)
/MCU_STM32G474/ENC_B: J802.4, U801.21 (PA7)
/MCU_STM32G474/ENC_BTN: J802.5, U801.19 (PA5)
/MCU_STM32G474/ISO_3V3A: C805.1, C807.1, C810.1, L801.2, U801.28 (VREF+), U801.29 (VDDA)
/MCU_STM32G474/NRST: C814.1, J803.12 (~RST), SW801.1, U801.7 (PG10)
/MCU_STM32G474/SWCLK: J803.6 (JCLK/SWCLK), U801.50 (PA14)
/MCU_STM32G474/SWDIO: J803.4 (JTMS/SWDIO), U801.49 (PA13)
/MCU_STM32G474/SWO: J803.8 (JTDO/SWO), U801.56 (PB3)
/MCU_STM32G474/Soft_NRST: C818.1, SW805.1, U801.60 (PB7)
/MCU_STM32G474/USB_DM: U801.45 (PA11), U802.3 (I/O2)
/MCU_STM32G474/USB_DP: U801.46 (PA12), U802.1 (I/O1)
/MCU_STM32G474/USR_BTN_1: C815.1, SW802.1, U801.55 (PD2)
/MCU_STM32G474/USR_BTN_2: C816.1, SW803.1, U801.18 (PA4)
/MCU_STM32G474/USR_BTN_3: C817.1, SW804.1, U801.59 (PB6)
/MCU_STM32G474/USR_LED_1: D801.2 (A), U801.51 (PA15)
/MCU_STM32G474/USR_LED_2: D802.2 (A), U801.52 (PC10)
/MCU_STM32G474/USR_LED_3: D803.2 (A), U801.53 (PC11); also elsewhere on the board
/MCU_STM32G474/USR_LED_4: D804.2 (A), U801.54 (PC12)
/MCU_STM32G474/VCP_RX: J803.13 (VCP_RX), U801.33 (PB11)
/MCU_STM32G474/VCP_TX: J803.14 (VCP_TX), U801.30 (PB10)
/MCU_STM32G474/V_USB: J801.A4 (VBUS), J801.A9 (VBUS), J801.B4 (VBUS), J801.B9 (VBUS), U802.5 (VBUS)
/NUCLEO_NRST: U801.24 (PB0); also elsewhere on the board
/NUCLEO_RX: U801.22 (PC4); also elsewhere on the board
/NUCLEO_TX: U801.23 (PC5); also elsewhere on the board
/Pwr_En: U801.37 (PB15); also elsewhere on the board
/U_Imes: U801.13 (PA1); also elsewhere on the board
/U_PWM_H: U801.14 (PA2); also elsewhere on the board
/U_PWM_L: U801.17 (PA3); also elsewhere on the board
/U_VPh: U801.12 (PA0); also elsewhere on the board
/V_Imes: U801.9 (PC1); also elsewhere on the board
/V_PWM_H: U801.38 (PC6); also elsewhere on the board
/V_PWM_L: U801.39 (PC7); also elsewhere on the board
/V_VPh: U801.8 (PC0); also elsewhere on the board
/W_Imes: U801.35 (PB13); also elsewhere on the board
/W_PWM_H: U801.40 (PC8); also elsewhere on the board
/W_PWM_L: U801.41 (PC9); also elsewhere on the board
/W_VPh: U801.25 (PB1); also elsewhere on the board
unnamed: D801.1 (K), R804.1
unnamed: D802.1 (K), R805.1
unnamed 122: D803.1 (K), R806.1; also elsewhere on the board
unnamed: D804.1 (K), R807.1
unnamed: J801.A5 (CC1), R802.1
unnamed: J801.B5 (CC2), R803.1
unnamed: R801.1, U801.61 (PB8)
unnamed: C801.2, U801.5 (PF0), Y801.2
unnamed: C802.2, U801.6 (PF1), Y801.1

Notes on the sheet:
USB connector + ESD protection 90 ohm impedance
ST-Link
Bypass capacitors 100nF as close to STM32 VDD as possible 10uF/1uF just next to 100nF 3V3A for VDDA and Vref
Connector for Encodeur (button)
Buttons Configure uC for pull-up on user buttons
I2C connector for display MDOB128064XV-YI
PBOOT0 - PB8
STM32G474RET6 uC
LEDS

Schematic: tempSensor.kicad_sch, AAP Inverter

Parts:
C1201: 100n; C_0402_1005Metric_Pad0.74x0.62mm_HandSolder
R1201: 200; R_0402_1005Metric_Pad0.72x0.64mm_HandSolder
U1201: TCN75A; SOIC-8_3.9x4.9mm_P1.27mm

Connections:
/I2C_SCL: U1201.2 (SCL); also elsewhere on the board
/I2C_SDA: U1201.1 (SDA); also elsewhere on the board
/ISO_3V3: C1201.1, R1201.2; also elsewhere on the board
/ISO_GND: C1201.2, U1201.4 (GND), U1201.5 (A2), U1201.6 (A1), U1201.7 (A0); also elsewhere on the board
unnamed: R1201.1, U1201.8 (VDD)

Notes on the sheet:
TCN75A : temp sensor I2C Address : 100 1xxx, xxx = A2,A1,A0

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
